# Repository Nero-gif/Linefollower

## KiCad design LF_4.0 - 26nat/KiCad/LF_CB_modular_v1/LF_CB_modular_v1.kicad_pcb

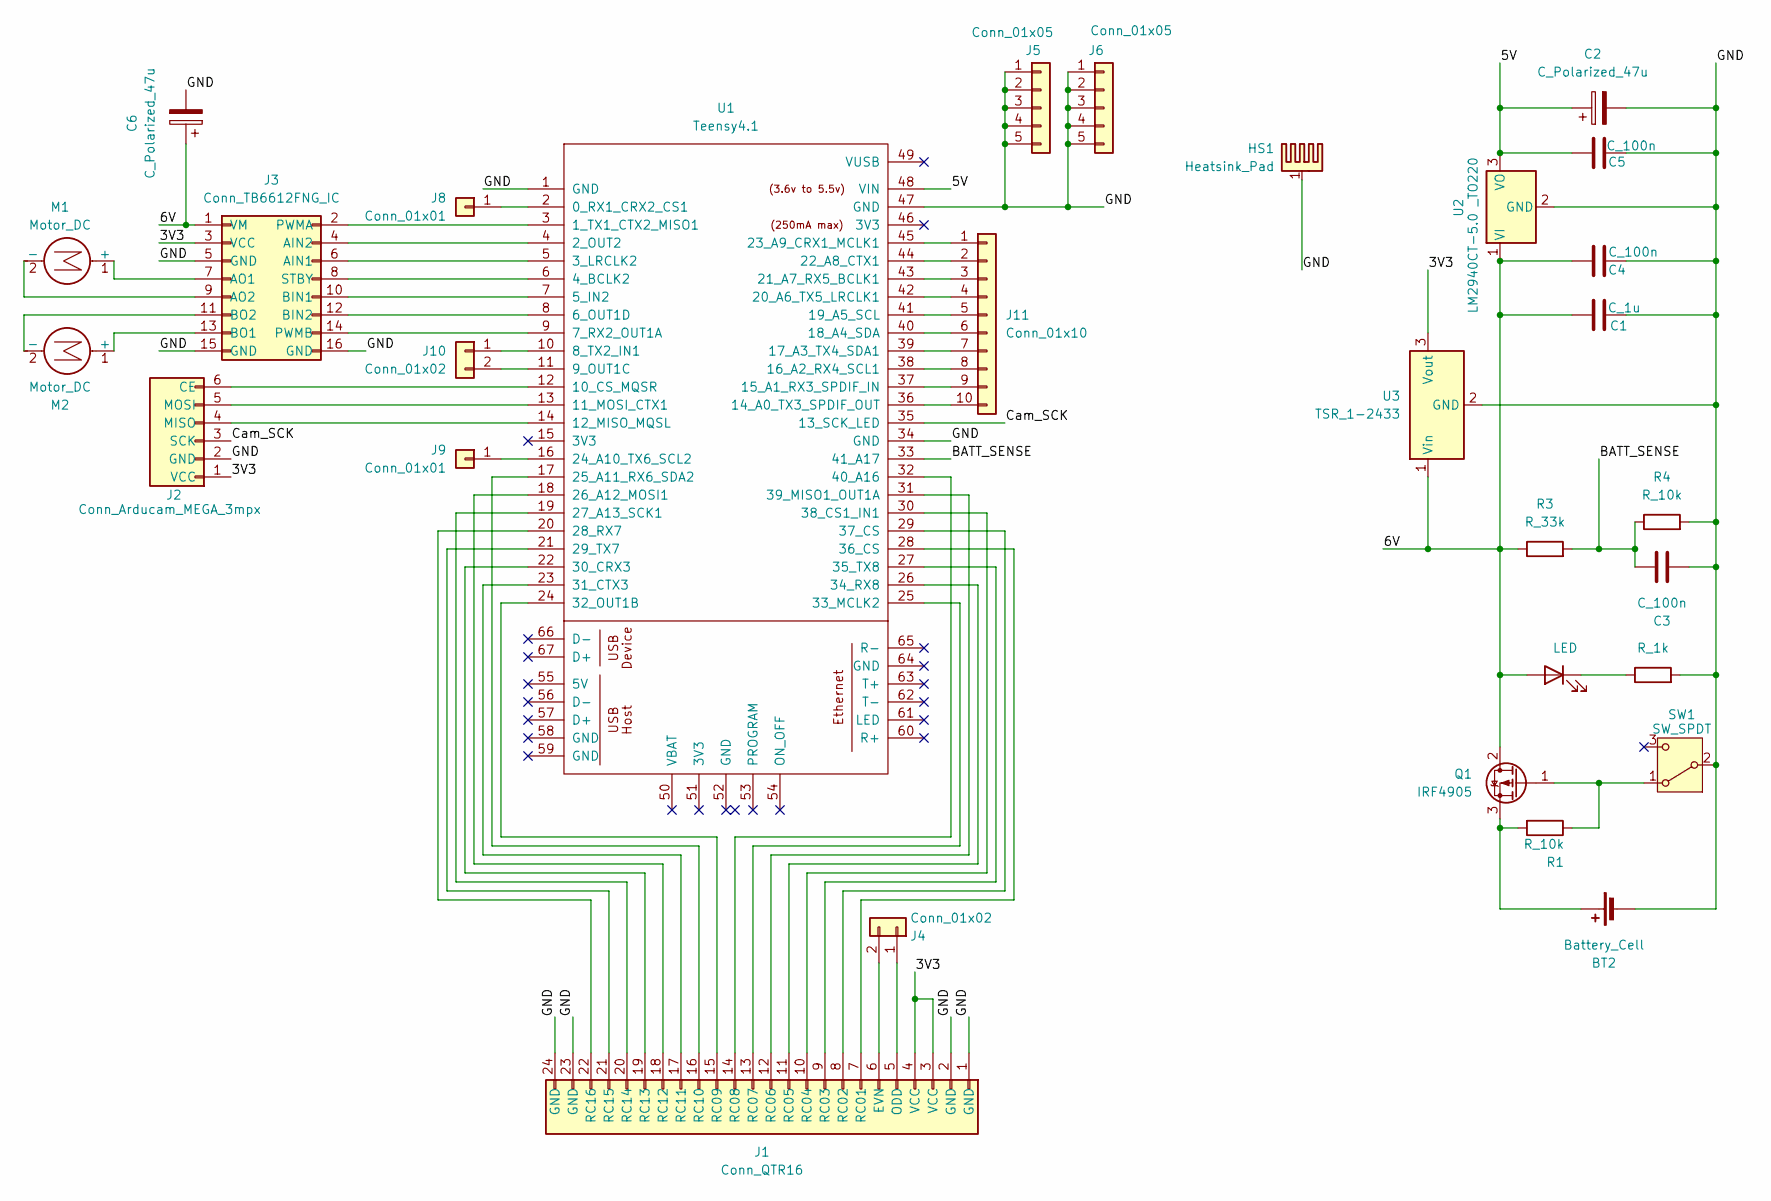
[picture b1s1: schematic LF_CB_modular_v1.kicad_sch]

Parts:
BT2: Battery_Cell; SolderWire-2sqmm_1x02_P7.8mm_D2mm_OD3.9mm
C1: C_1u; C_Disc_D5.0mm_W2.5mm_P5.00mm
C2, C6: C_Polarized_47u; CP_Radial_D6.3mm_P2.50mm
C3, C4, C5: C_100n; C_Disc_D4.3mm_W1.9mm_P5.00mm
D1: LED; LED_D5.0mm
HS1: Heatsink_Pad; Heatsink_HS-123-25_TO220_STONECOLD
J1: Conn_QTR16; IDC-Header_2x12_P2.54mm_Vertical
J2: Conn_Arducam_MEGA_3mpx; JST_XH_B6B-XH-A_1x06_P2.50mm_Vertical
J3: Conn_TB6612FNG_IC; PinHeader_TB6612FNG_IC
J4, J10: Conn_01x02; PinSocket_1x02_P2.54mm_Vertical
J5, J6: Conn_01x05; PinSocket_1x05_P2.54mm_Vertical
J8, J9: Conn_01x01; PinSocket_1x01_P2.54mm_Vertical
J11: Conn_01x10; PinSocket_1x10_P2.54mm_Vertical
M1, M2: Motor_DC; JST_XH_B2B-XH-A_1x02_P2.50mm_Vertical
Q1: IRF4905; TO-220-3_Vertical
R1, R4: R_10k; R_Axial_DIN0204_L3.6mm_D1.6mm_P7.62mm_Horizontal
R2: R_1k; R_Axial_DIN0204_L3.6mm_D1.6mm_P7.62mm_Horizontal
R3: R_33k; R_Axial_DIN0204_L3.6mm_D1.6mm_P7.62mm_Horizontal
SW1: SW_SPDT; JST_XH_B2B-XH-A_1x02_P2.50mm_Vertical
U1: Teensy4.1; Teensy41_lite
U2: LM2940CT-5.0 _TO220; TO-220-3_Vertical
U3: TSR_1-2433; Converter_DCDC_TRACO_TSR-1_THT

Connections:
/3V3: J1.3 (VCC), J1.4 (VCC), J2.1 (VCC), J3.3 (VCC), U3.3 (Vout)
/5V: C2.1, C5.2, U1.48 (VIN), U2.3 (VO)
/6V: C1.1, C4.2, C6.1, D1.2 (A), J3.1 (VM), Q1.2 (D), R3.1, U2.1 (VI), U3.1 (Vin)
/BATT_SENSE: C3.2, R3.2, R4.1, U1.33 (41_A17)
/Cam_SCK: J2.3 (SCK), U1.35 (13_SCK_LED)
/GND: BT2.2 (-), C1.2, C2.2, C3.1, C4.1, C5.1, C6.2, HS1.1, J1.1 (GND), J1.2 (GND), J1.23 (GND), J1.24 (GND), J2.2 (GND), J3.5 (GND), J3.15 (GND), J3.16 (GND), J5.1, J5.2, J5.3, J5.4, J5.5, J6.1, J6.2, J6.3, J6.4, J6.5, R2.2, R4.2, SW1.2 (B), U1.1 (GND), U1.34 (GND), U1.47 (GND), U2.2 (GND), U3.2 (GND)
unnamed: BT2.1 (+), Q1.3 (S), R1.2
unnamed: D1.1 (K), R2.1
unnamed: J1.6 (EVN), J4.2
unnamed: J1.5 (ODD), J4.1
unnamed: J1.7 (RC01), U1.28 (36_CS)
unnamed: J1.8 (RC02), U1.29 (37_CS)
unnamed: J1.9 (RC03), U1.27 (35_TX8)
unnamed: J1.10 (RC04), U1.30 (38_CS1_IN1)
unnamed: J1.11 (RC05), U1.26 (34_RX8)
unnamed: J1.12 (RC06), U1.31 (39_MISO1_OUT1A)
unnamed: J1.13 (RC07), U1.25 (33_MCLK2)
unnamed: J1.14 (RC08), U1.32 (40_A16)
unnamed: J1.15 (RC09), U1.24 (32_OUT1B)
unnamed: J1.16 (RC10), U1.17 (25_A11_RX6_SDA2)
unnamed: J1.17 (RC11), U1.23 (31_CTX3)
unnamed: J1.18 (RC12), U1.18 (26_A12_MOSI1)
unnamed: J1.19 (RC13), U1.22 (30_CRX3)
unnamed: J1.20 (RC14), U1.19 (27_A13_SCK1)
unnamed: J1.21 (RC15), U1.21 (29_TX7)
unnamed: J1.22 (RC16), U1.20 (28_RX7)
unnamed: J2.6 (CE), U1.12 (10_CS_MQSR)
unnamed: J2.4 (MISO), U1.14 (12_MISO_MQSL)
unnamed: J2.5 (MOSI), U1.13 (11_MOSI_CTX1)
unnamed: J3.6 (AIN1), U1.5 (3_LRCLK2)
unnamed: J3.4 (AIN2), U1.4 (2_OUT2)
unnamed: J3.7 (AO1), M1.1 (+)
unnamed: J3.9 (AO2), M1.2 (-)
unnamed: J3.10 (BIN1), U1.7 (5_IN2)
unnamed: J3.12 (BIN2), U1.8 (6_OUT1D)
unnamed: J3.13 (BO1), M2.1 (+)
unnamed: J3.11 (BO2), M2.2 (-)
unnamed: J3.2 (PWMA), U1.3 (1_TX1_CTX2_MISO1)
unnamed: J3.14 (PWMB), U1.9 (7_RX2_OUT1A)
unnamed: J3.8 (STBY), U1.6 (4_BCLK2)
unnamed: J8.1, U1.2 (0_RX1_CRX2_CS1)
unnamed: J9.1, U1.16 (24_A10_TX6_SCL2)
unnamed: J10.1, U1.10 (8_TX2_IN1)
unnamed: J10.2, U1.11 (9_OUT1C)
unnamed: J11.1, U1.45 (23_A9_CRX1_MCLK1)
unnamed: J11.2, U1.44 (22_A8_CTX1)
unnamed: J11.3, U1.43 (21_A7_RX5_BCLK1)
unnamed: J11.4, U1.42 (20_A6_TX5_LRCLK1)
unnamed: J11.5, U1.41 (19_A5_SCL)
unnamed: J11.6, U1.40 (18_A4_SDA)
unnamed: J11.7, U1.39 (17_A3_TX4_SDA1)
unnamed: J11.8, U1.38 (16_A2_RX4_SCL1)
unnamed: J11.9, U1.37 (15_A1_RX3_SPDIF_IN)
unnamed: J11.10, U1.36 (14_A0_TX3_SPDIF_OUT)
unnamed: Q1.1 (G), R1.1, SW1.1 (A)

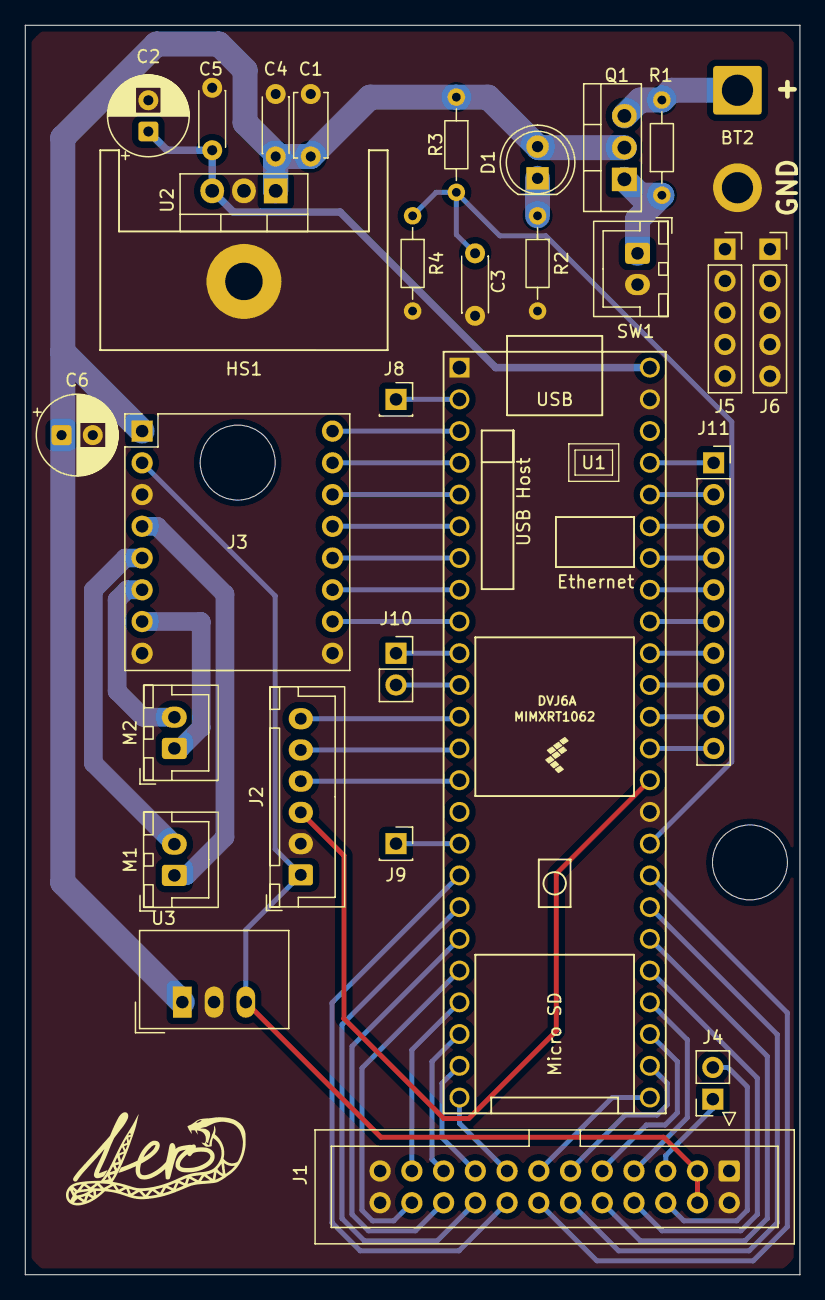
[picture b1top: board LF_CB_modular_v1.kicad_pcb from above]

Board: 2 copper layers, 62.0 x 100.0 mm, 30 parts (0 on the bottom side), 55 nets.

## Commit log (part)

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2026-02-02 starting fucking linefollower coding
2026-02-02 main
2026-02-02 testing pico
2026-02-02 helloWorld
2026-02-02 test ESP vrtula funguje
2026-02-02 skill issue
2026-02-03 turbína ok, ale odletí vozítko
2026-02-04 odletame
2026-02-19 Initial plan
